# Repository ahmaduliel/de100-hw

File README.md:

# de100-hw
Design PCB for DE100 extension

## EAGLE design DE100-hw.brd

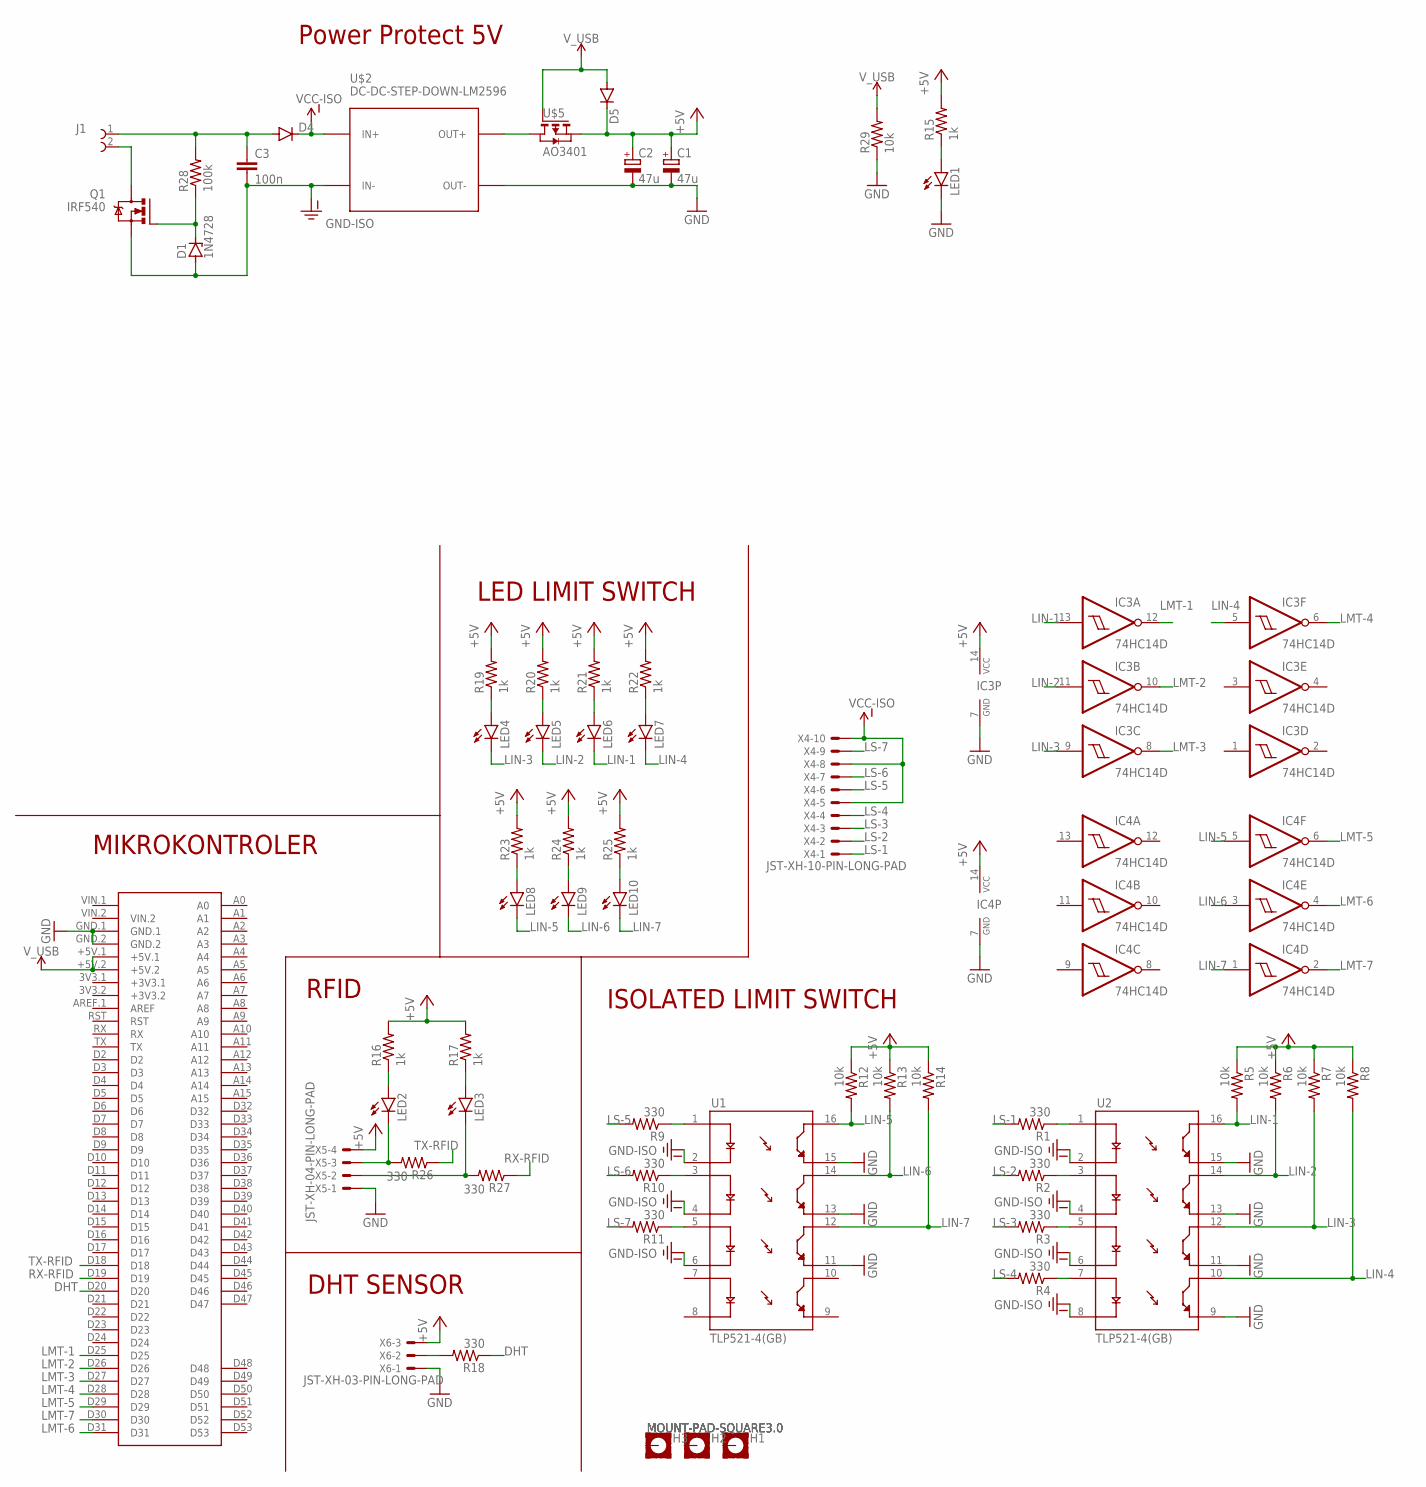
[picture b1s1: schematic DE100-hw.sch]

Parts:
C1, C2: 47u; UD-6,3X5,8_NICHICON
C3: 100n; C0805K
D1: 1N4728; DO41Z10
D4, D5: DIODE-DO-214AC; DO-214AC
H1, H2, H3: MOUNT-PAD-SQUARE3.0; 3,0-PAD-SQUARE
IC3, IC4: 74HC14D; SO14
J1: 691312510002
LED1, LED2, LED3, LED4, LED5, LED6, LED7, LED8, LED9, LED10: LEDCHIPLED_0805; CHIPLED_0805
Q1: IRF540; TO220BV
R1, R2, R3, R4, R9, R10, R11, R18, R26, R27: 330; R0805
R5, R6, R7, R8, R12, R13, R14, R29: 10k; R0805
R15, R16, R17, R19, R20, R21, R22, R23, R24, R25: 1k; R0805
R28: 100k; R0805
U1, U2: TLP521-4(GB); DIP762W50P254L2007H485Q16
U$1: MEGA2560_MIKRO
U$2: DC-DC-STEP-DOWN-LM2596
U$5: AO3401; SOT23
X4: JST-XH-10-PIN-LONG-PAD; JST-XH-10-PACKAGE-LONG-PAD
X5: JST-XH-04-PIN-LONG-PAD; JST-XH-04-PACKAGE-LONG-PAD
X6: JST-XH-03-PIN-LONG-PAD; JST-XH-03-PACKAGE-LONG-PAD

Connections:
+5V: C1.+, C2.+, D5.C, IC3.14 (VCC), IC4.14 (VCC), R5.1, R6.1, R7.1, R8.1, R12.1, R13.1, R14.1, R15.2, R16.2, R17.2, R19.2, R20.2, R21.2, R22.2, R23.2, R24.2, R25.2, U$5.2 (S), X5.4, X6.3
DHT: R18.1, U$1.D20
GND: C1.-, C2.-, IC3.7 (GND), IC4.7 (GND), LED1.C, R29.1, U1.11 (ET3), U1.13 (ET2), U1.15 (ET1), U2.9 (ET4), U2.11 (ET3), U2.13 (ET2), U2.15 (ET1), U$1.GND.1, U$1.GND.2, U$2.OUT-, X5.1, X6.1
GND-ISO: C3.2, D1.A, Q1.S, U1.2 (C1), U1.4 (C2), U1.6 (C3), U2.2 (C1), U2.4 (C2), U2.6 (C3), U2.8 (C4), U$2.IN-
LIN-1: IC3.13 (I), LED6.C, R5.2, U2.16 (CT1)
LIN-2: IC3.11 (I), LED5.C, R6.2, U2.14 (CT2)
LIN-3: IC3.9 (I), LED4.C, R7.2, U2.12 (CT3)
LIN-4: IC3.5 (I), LED7.C, R8.2, U2.10 (CT4)
LIN-5: IC4.5 (I), LED8.C, R12.2, U1.16 (CT1)
LIN-6: IC4.3 (I), LED9.C, R13.2, U1.14 (CT2)
LIN-7: IC4.1 (I), LED10.C, R14.2, U1.12 (CT3)
LMT-1: IC3.12 (O), U$1.D25
LMT-2: IC3.10 (O), U$1.D26
LMT-3: IC3.8 (O), U$1.D27
LMT-4: IC3.6 (O), U$1.D28
LMT-5: IC4.6 (O), U$1.D29
LMT-6: IC4.4 (O), U$1.D31
LMT-7: IC4.2 (O), U$1.D30
LS-1: R1.2, X4.1
LS-2: R2.2, X4.2
LS-3: R3.2, X4.3
LS-4: R4.2, X4.4
LS-5: R9.2, X4.6
LS-6: R10.2, X4.7
LS-7: R11.2, X4.9
unnamed: J1.2, Q1.D
unnamed: U$2.OUT+, U$5.3 (D)
unnamed: D1.C, Q1.G, R28.1
unnamed: C3.1, D4.A, J1.1, R28.2
unnamed: LED1.A, R15.1
unnamed: LED2.A, R16.1
unnamed: LED3.A, R17.1
unnamed: R1.1, U2.1 (A1)
unnamed: R2.1, U2.3 (A2)
unnamed: R3.1, U2.5 (A3)
unnamed: R4.1, U2.7 (A4)
unnamed: R9.1, U1.1 (A1)
unnamed: R10.1, U1.3 (A2)
unnamed: R11.1, U1.5 (A3)
unnamed: LED2.C, R26.2, X5.3
unnamed: LED3.C, R27.2, X5.2
unnamed: LED4.A, R19.1
unnamed: R18.2, X6.2
unnamed: LED5.A, R20.1
unnamed: LED6.A, R21.1
unnamed: LED7.A, R22.1
unnamed: LED8.A, R23.1
unnamed: LED9.A, R24.1
unnamed: LED10.A, R25.1
RX-RFID: R27.1, U$1.D19
TX-RFID: R26.1, U$1.D18
VCC-ISO: D4.C, U$2.IN+, X4.5, X4.8, X4.10
V_USB: D5.A, R29.2, U$1.+5V.1, U$1.+5V.2, U$5.1 (G)

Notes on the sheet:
Power Protect 5V
MIKROKONTROLER
LED LIMIT SWITCH
RFID
DHT SENSOR
ISOLATED LIMIT SWITCH

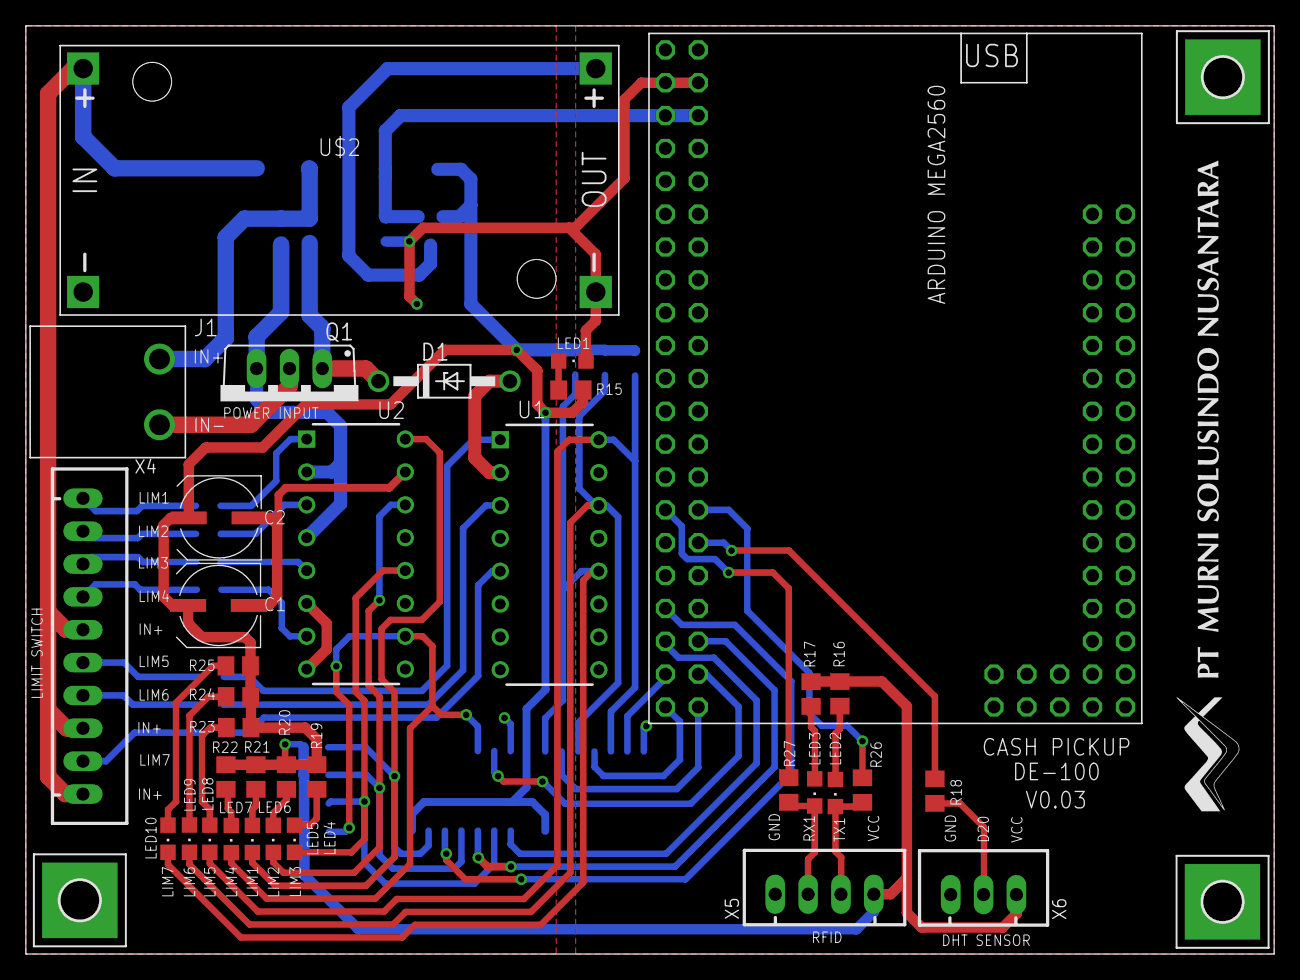
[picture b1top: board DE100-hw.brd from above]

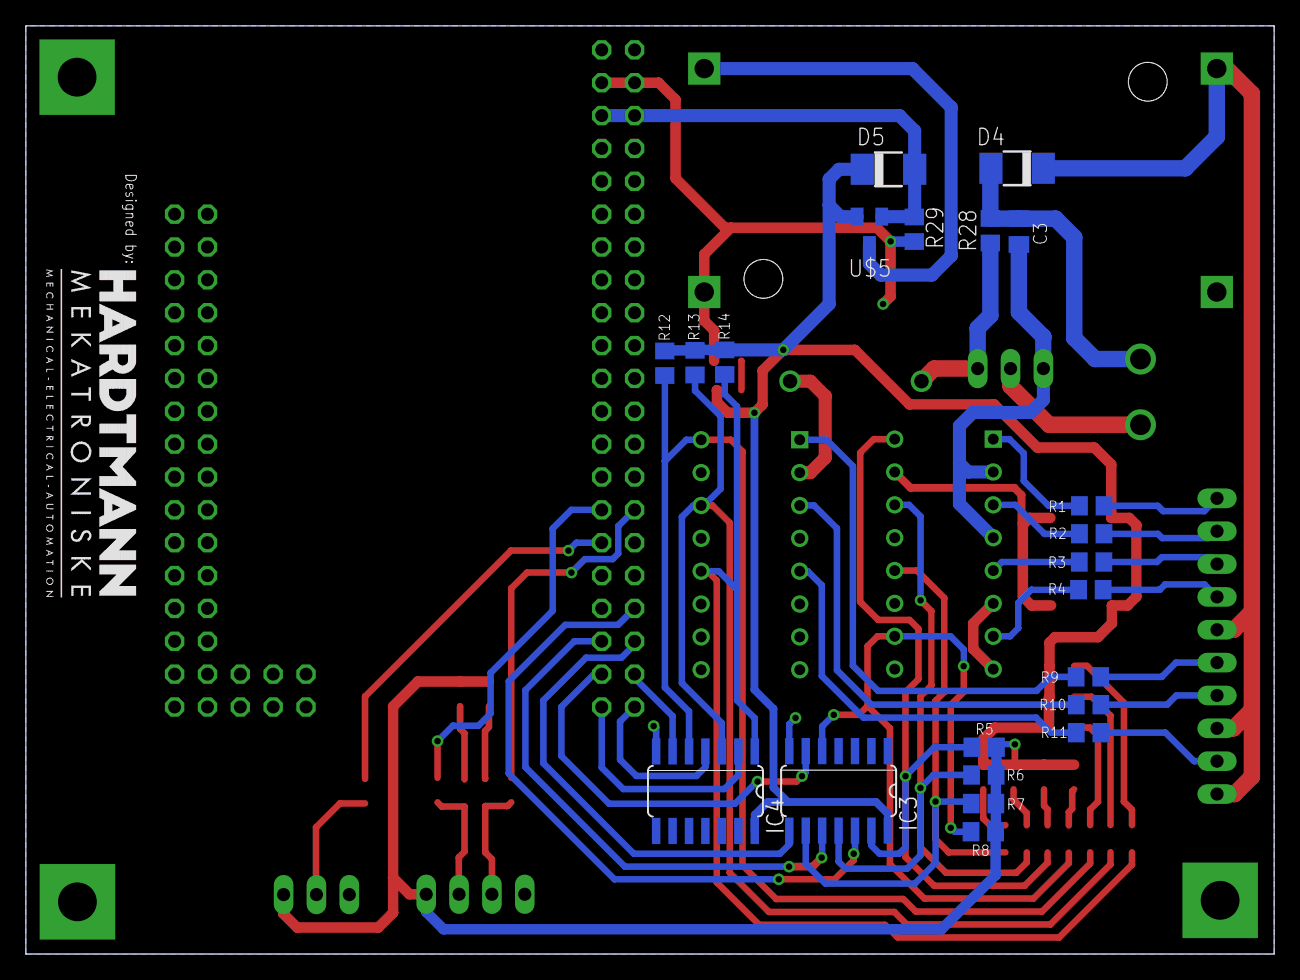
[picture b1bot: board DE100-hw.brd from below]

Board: 2 copper layers, 96.5 x 71.8 mm, 60 parts (22 on the bottom side), 53 nets.

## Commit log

2020-05-13 add desain v1
2020-05-13 change route
2020-05-14 add additional name and gerber file
2020-05-14 add hole
2020-05-14 change logo murni
2020-05-15 order for multikarya
2020-05-28 post production revision
2020-05-28 change molex connector library
2020-05-29 change position component and logo HM
2020-06-12 last dev #1 production
2020-11-09 add power protection

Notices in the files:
parts and their libraries:
diy-modules: Released under the Creative Commons Attribution 4.0 International License: http://creativecommons.org/licenses/by/4.0
Wurth_Elektronik_Electromechanic_Termina: Copyright: Würth Elektronik
